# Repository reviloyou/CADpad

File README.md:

# CAD-hackpad
A macropad made to optimize commonly used commands/actions in Soldiworks CAD. Claude used for the program export onto the CADpad

## Simple-ish explanation of project
It is split up into 6 buttons and 1 knob with diffrent purposes. This includes a button for choosing the plane/a plane, sketching on that plane, extruding as well as cutting and a simple enter button. Then its onto the last button and knob, the knobs rotation is used for adjusting numbers up and down in intervalls of (1-10-25)mm. Adjusting the interval is done with the button and the rotary encoder button is used for rounding this chosen number in solidworks to the closest 10. 

This project is supposed to effectivize CAD work but wont replace a regular keyboard and mouse. It bypasses some of the most repetetive mouse clicks that are usual for solidworks or CAD in general.

## Case assembly
The case assembly is split into a simple top and bottom. This can be 3D printed and is made so that this sanwich ice-cream looking hackpad doesnt feature any visible screws. On the top part of the case you can see 3 holes: these holes are intended to fit the guide-stick on the bottom case, as well as, 2 M3 heat innset. This makes it so that the screws can be secured safely and threaded through the bottom case making it so that no screws are visible. For assembly after getting the heatset innserts put in is simple: Line up the soldered PCB pointing seeduino down and beeing able to read "thy barbiemann", you also have to make sure that the seeduino is pointed towards the output port. Then you simply have 2 screws for easy accessibility.

## Bill of materials
1x XIAO RP2040
6x Cherry MX Switches
6x Blank DSA Keycaps
1x EC11 20mm Rotary Encoders
2x M3x16 Bolt
2x M3 Heatset

## Schematic (a little messy)

## PCB

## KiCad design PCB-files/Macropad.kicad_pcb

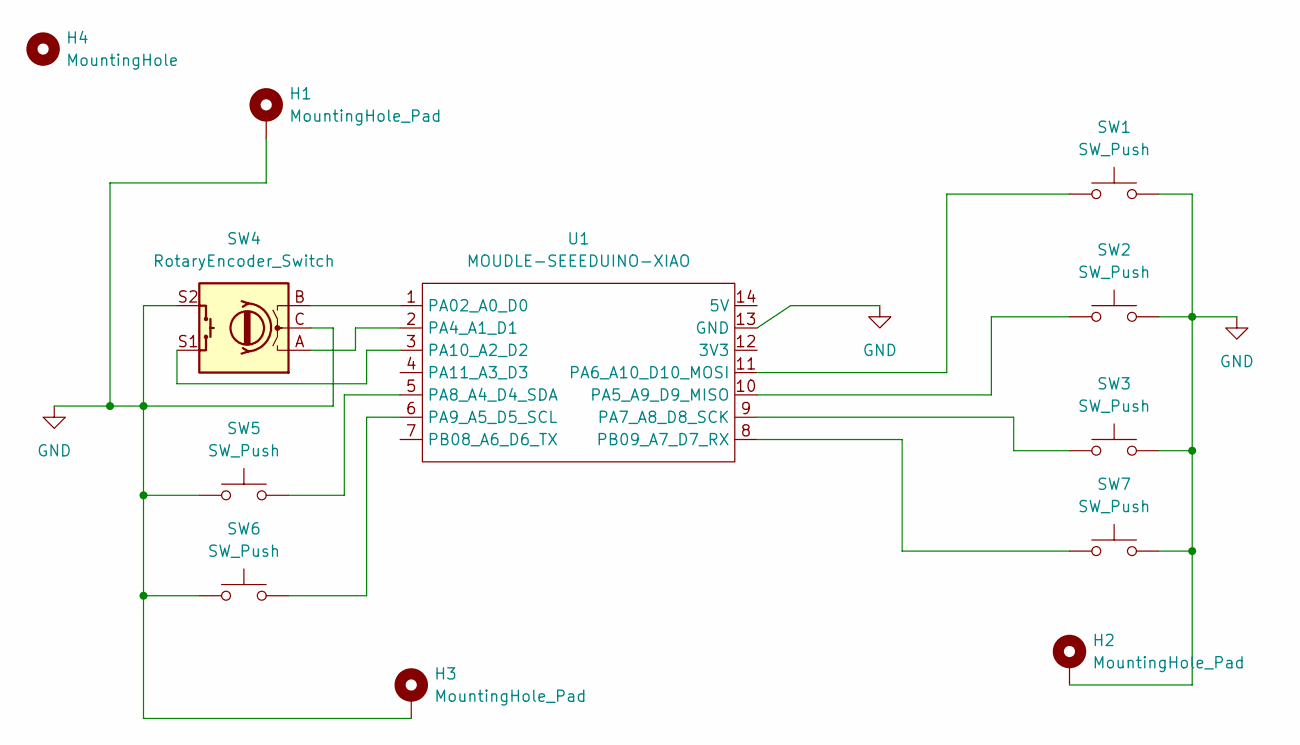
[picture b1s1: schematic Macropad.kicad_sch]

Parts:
H1, H2, H3: MountingHole_Pad; MountingHole_3.2mm_M3_Pad
H4: MountingHole; MountingHole_2.2mm_M2
SW1, SW2, SW3, SW5, SW6, SW7: SW_Push; SW_Cherry_MX_1.00u_PCB
SW4: RotaryEncoder_Switch; RotaryEncoder_Alps_EC12E-Switch_Vertical_H20mm
U1: MOUDLE-SEEEDUINO-XIAO; XIAO-Generic-Hybrid-14P-2.54-21X17.8MM

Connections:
GND: H1.1 (1_1), H2.1 (1_1), H3.1 (1_1), SW1.2, SW2.2, SW3.2, SW4.C, SW4.S2, SW5.1, SW6.1, SW7.2, U1.13 (GND)
unnamed: SW4.B, U1.1 (PA02_A0_D0)
unnamed: SW4.A, U1.2 (PA4_A1_D1)
unnamed: SW2.1, U1.10 (PA5_A9_D9_MISO)
unnamed: SW1.1, U1.11 (PA6_A10_D10_MOSI)
unnamed: SW3.1, U1.9 (PA7_A8_D8_SCK)
unnamed: SW5.2, U1.5 (PA8_A4_D4_SDA)
unnamed: SW6.2, U1.6 (PA9_A5_D5_SCL)
unnamed: SW4.S1, U1.3 (PA10_A2_D2)
unnamed: SW7.1, U1.8 (PB09_A7_D7_RX)

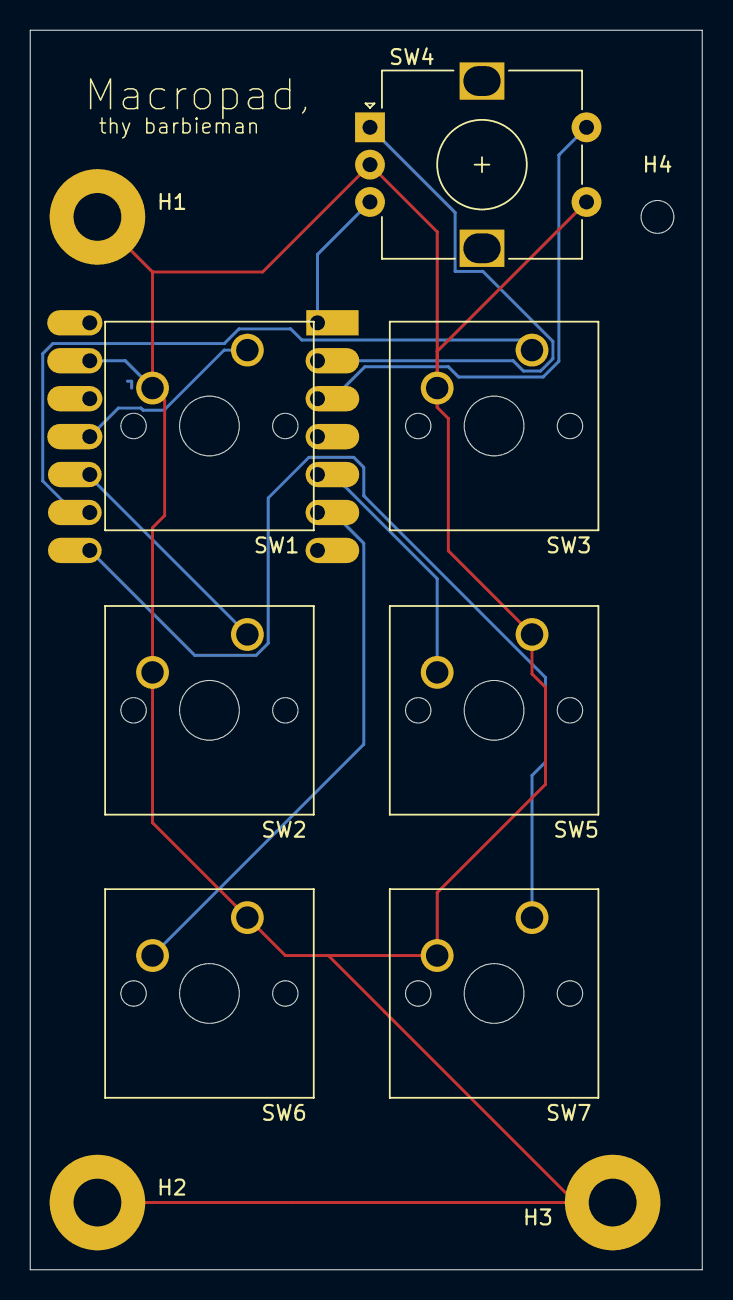
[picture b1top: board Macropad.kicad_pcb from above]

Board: 2 copper layers, 45.0 x 83.0 mm, 12 parts (1 on the bottom side), 10 nets.
